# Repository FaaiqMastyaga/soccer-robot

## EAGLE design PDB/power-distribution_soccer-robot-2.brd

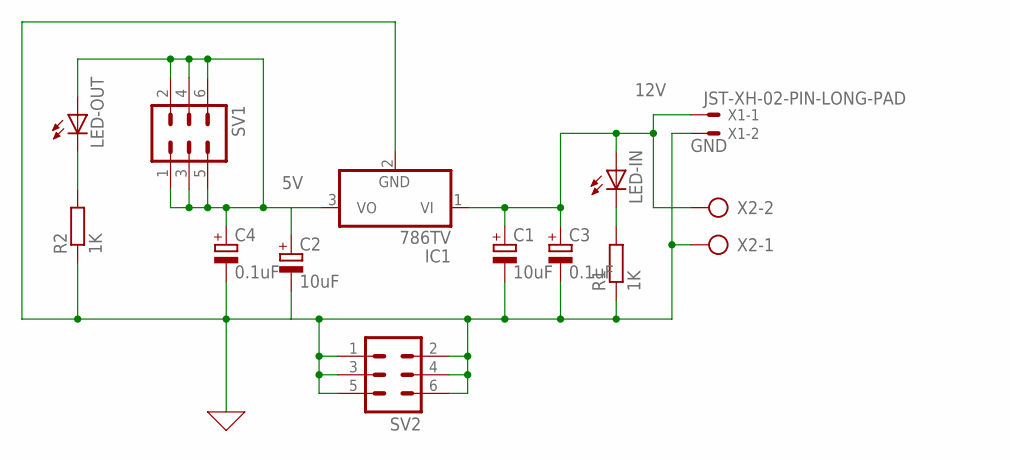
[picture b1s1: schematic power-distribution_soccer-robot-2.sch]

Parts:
C1, C2: 10uF; E2,5-6E
C3, C4: 0.1uF; E2,5-6E
IC1: 786TV; TO220V
LED-IN: LED5MM
LED-OUT: LED5MM
R1, R2: 1K; 0204/5
SV1, SV2: MA03-2; MA03-2(2)
X1: JST-XH-02-PIN-LONG-PAD; JST-XH-02-PACKAGE-LONG-PAD
X2: AK500/2-H

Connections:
5V: C2.+, C4.+, IC1.3 (VO), LED-OUT.A, SV1.1, SV1.2, SV1.3, SV1.4, SV1.5, SV1.6
12V: C1.+, C3.+, IC1.1 (VI), LED-IN.A, X1.1, X2.2
GND: C1.-, C2.-, C3.-, C4.-, IC1.2 (GND), R1.1, R2.1, SV2.1, SV2.2, SV2.3, SV2.4, SV2.5, SV2.6, X1.2, X2.1
unnamed: LED-OUT.K (C), R2.2
unnamed: LED-IN.K (C), R1.2

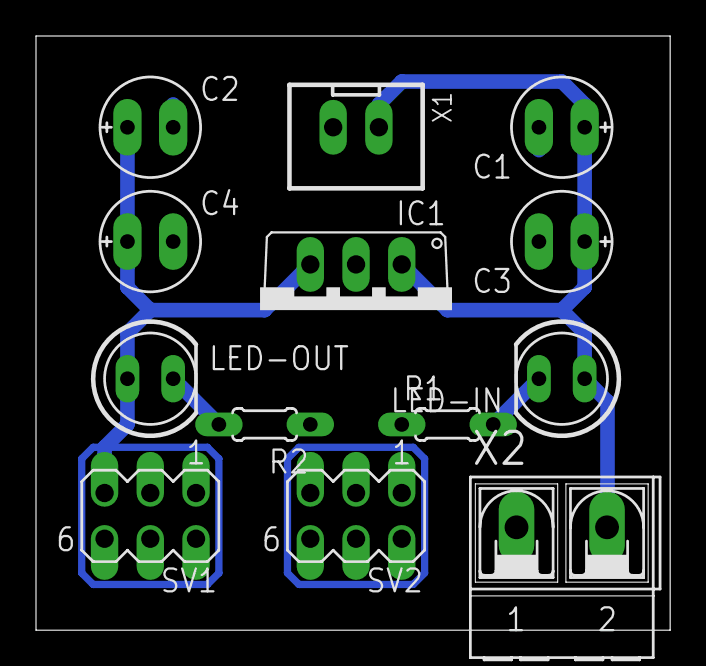
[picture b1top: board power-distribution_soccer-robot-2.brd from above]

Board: 2 copper layers, 35.2 x 33.0 mm, 13 parts (0 on the bottom side), 5 nets.

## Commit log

2025-02-24 feat: add arduino source code
2025-02-24 feat: add electrical schematic
2025-02-24 feat: add 3d design
2025-02-24 feat: add application source code
